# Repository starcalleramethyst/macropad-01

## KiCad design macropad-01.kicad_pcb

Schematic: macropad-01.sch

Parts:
C1: 10uF; C_0805_2012Metric
C2, C3, C6: 0.1uF; C_0805_2012Metric
C4, C5: 22pF; C_0805_2012Metric
C7: 1uF; C_0805_2012Metric
D1, D2, D3, D4: D_Small; D_SOD-123
F1: 500mA; Fuse_1206_3216Metric
MX1, MX2, MX3, MX4: MX-NoLED; MX-1U-NoLED
R1, R2: 22; R_0805_2012Metric
R3, R4: 10k; R_0805_2012Metric
SW1: SW_Push; Reset_Pretty
U1: ATmega32U4-AU; TQFP-44_10x10mm_P0.8mm
USB1: Molex-0548190589
Y1: 16MHz; Crystal_SMD_3225-4Pin_3.2x2.5mm

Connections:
+5V: C1.1, C2.1, C3.1, C6.1, F1.1, R3.1, U1.7 (VBUS), U1.14 (VCC), U1.24 (AVCC), U1.34 (VCC), U1.44 (AVCC)
COL0: MX1.1, MX2.1, U1.29 (PB5)
COL1: MX3.1, MX4.1, U1.28 (PB4)
D+: R2.2, USB1.3
D-: R1.2, USB1.4
GND: C1.2, C2.2, C3.2, C4.2, C5.2, C6.2, C7.2, R4.2, SW1.1, U1.5 (UGND), U1.15 (GND), U1.23 (GND), U1.35 (GND), U1.43 (GND), USB1.1, Y1.1, Y1.3
unnamed: C4.1, U1.17 (XTAL1), Y1.4
unnamed: C5.1, U1.16 (XTAL2), Y1.2
unnamed: C7.1, U1.6 (UCAP)
unnamed: D1.2, MX1.2
unnamed: D2.2, MX2.2
unnamed: D3.2, MX3.2
unnamed: D4.2, MX4.2
unnamed: R1.1, U1.3 (D-)
unnamed: R2.1, U1.4 (D+)
unnamed: R3.2, SW1.2, U1.13 (~RESET)
ROW0: D1.1, D3.1, U1.27 (PD7)
ROW1: D2.1, D4.1, U1.30 (PB6)
VCC: F1.2, USB1.5

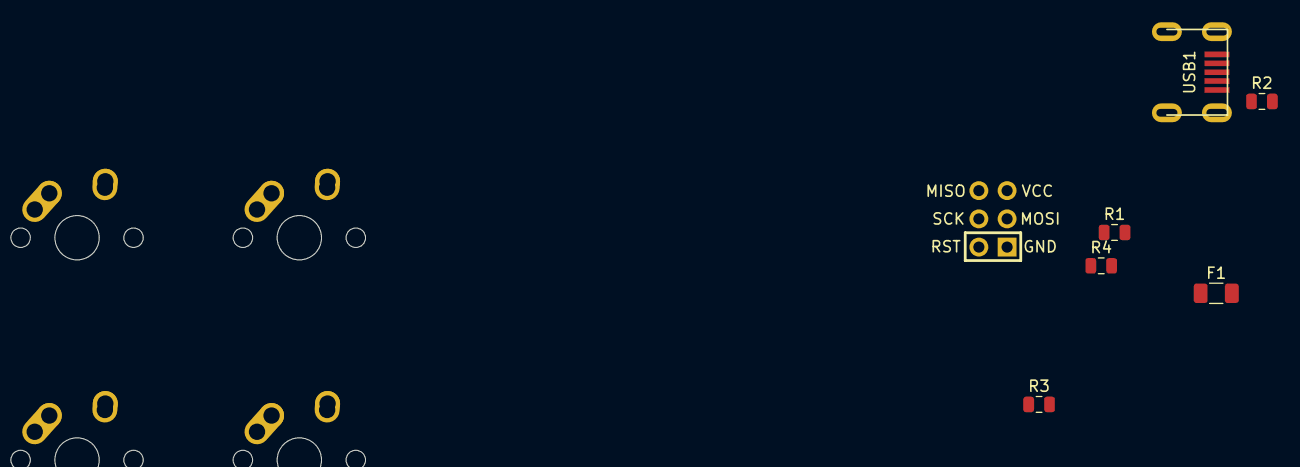
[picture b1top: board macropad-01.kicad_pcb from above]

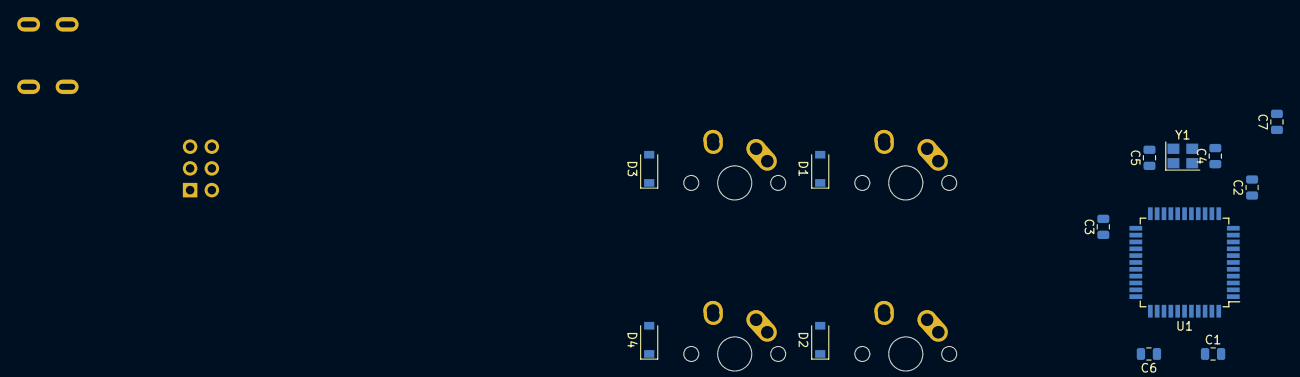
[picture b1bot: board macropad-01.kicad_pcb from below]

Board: 2 copper layers, 24 parts (13 on the bottom side), 19 nets, no tracks yet.

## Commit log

2020-03-30 Initialize Kicad project
2020-03-30 Add submodeules
2020-03-30 added component libraries
2020-03-30 mid step-3 pause
2020-04-06 working through guide
    next step is reset button
2020-04-06 schematic complete
2020-04-06 started formatting pcb
